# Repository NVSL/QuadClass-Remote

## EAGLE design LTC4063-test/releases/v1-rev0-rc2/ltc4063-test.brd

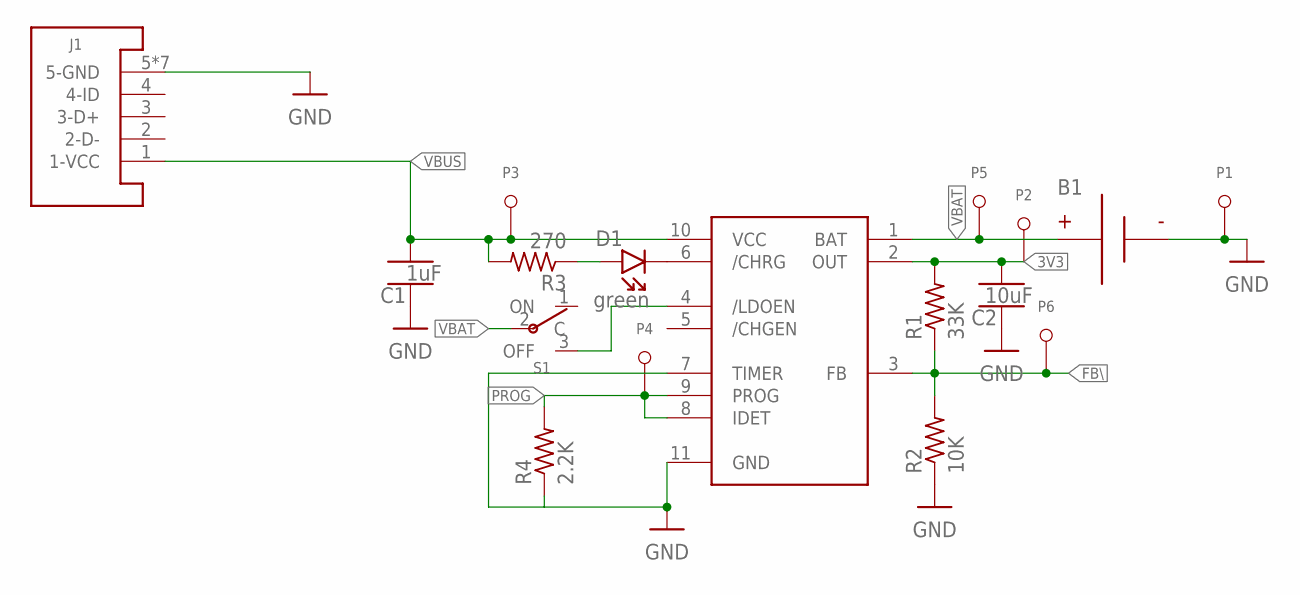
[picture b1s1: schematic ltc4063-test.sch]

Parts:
B1: BATTERY-SPRING-SMD; WIRE-TERMINAL-1X2-2.5MM-SMD-AVX-009276002021106
C1: 1uF; CAPC2012X140_HS
C2: 10uF; CAPC2012X140_HS
D1: green; LEDSC125X200X120-2_HS
J1: USB-MICROA-AMPHENOL-10118192-0001LF; USB-MICROA-10118192-0001LF
P1, P2, P3, P4, P5, P6: TEST-POINT; TEST-POINT-KEYSTONE-5000
R1: 33K; RESC2012X60_HS
R2: 10K; RESC2012X60_HS
R3: 270; RESC2012X60_HS
R4: 2.2K; RESC2012X60_HS
S1: POWER-SWITCH-MFS201N-9-Z-SMD-VERTICAL; JS102011JCQN
U1: LIPO-VREG-LTC4063; SON50P300X300X80-11T165X238

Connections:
3V3: C2.2, P2.T, R1.2, U1.2 (OUT)
FB\: P6.T, R1.1, R2.2, U1.3 (FB)
GND: B1.2A (N), B1.2B (N), C1.1, C2.1, J1.5 (5-GND), J1.6 (5-GND), J1.7 (5-GND), J1.8 (5-GND), J1.9 (5-GND), J1.10 (5-GND), J1.11 (5-GND), P1.T, R2.1, R4.1, U1.7 (TIMER), U1.11 (GND)
unnamed: S1.3 (OFF), U1.4 (/LDOEN)
unnamed: D1.C, U1.6 (/CHRG)
unnamed: D1.A, R3.1
PROG: P4.T, R4.2, U1.8 (IDET), U1.9 (PROG)
VBAT: B1.1A, B1.1B, P5.T, S1.2 (C), U1.1 (BAT)
VBUS: C1.2, J1.1 (1-VCC), P3.T, R3.2, U1.10 (VCC)

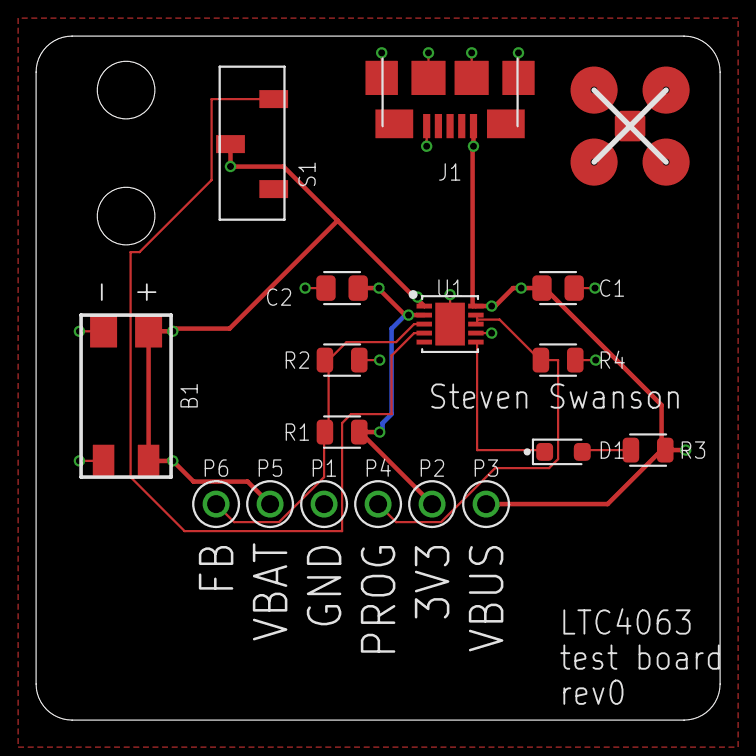
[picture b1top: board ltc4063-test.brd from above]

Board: 2 copper layers, 38.0 x 38.0 mm, 18 parts (0 on the bottom side), 9 nets.

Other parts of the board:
U$1: QUADCLASS_LOGO_SMALL

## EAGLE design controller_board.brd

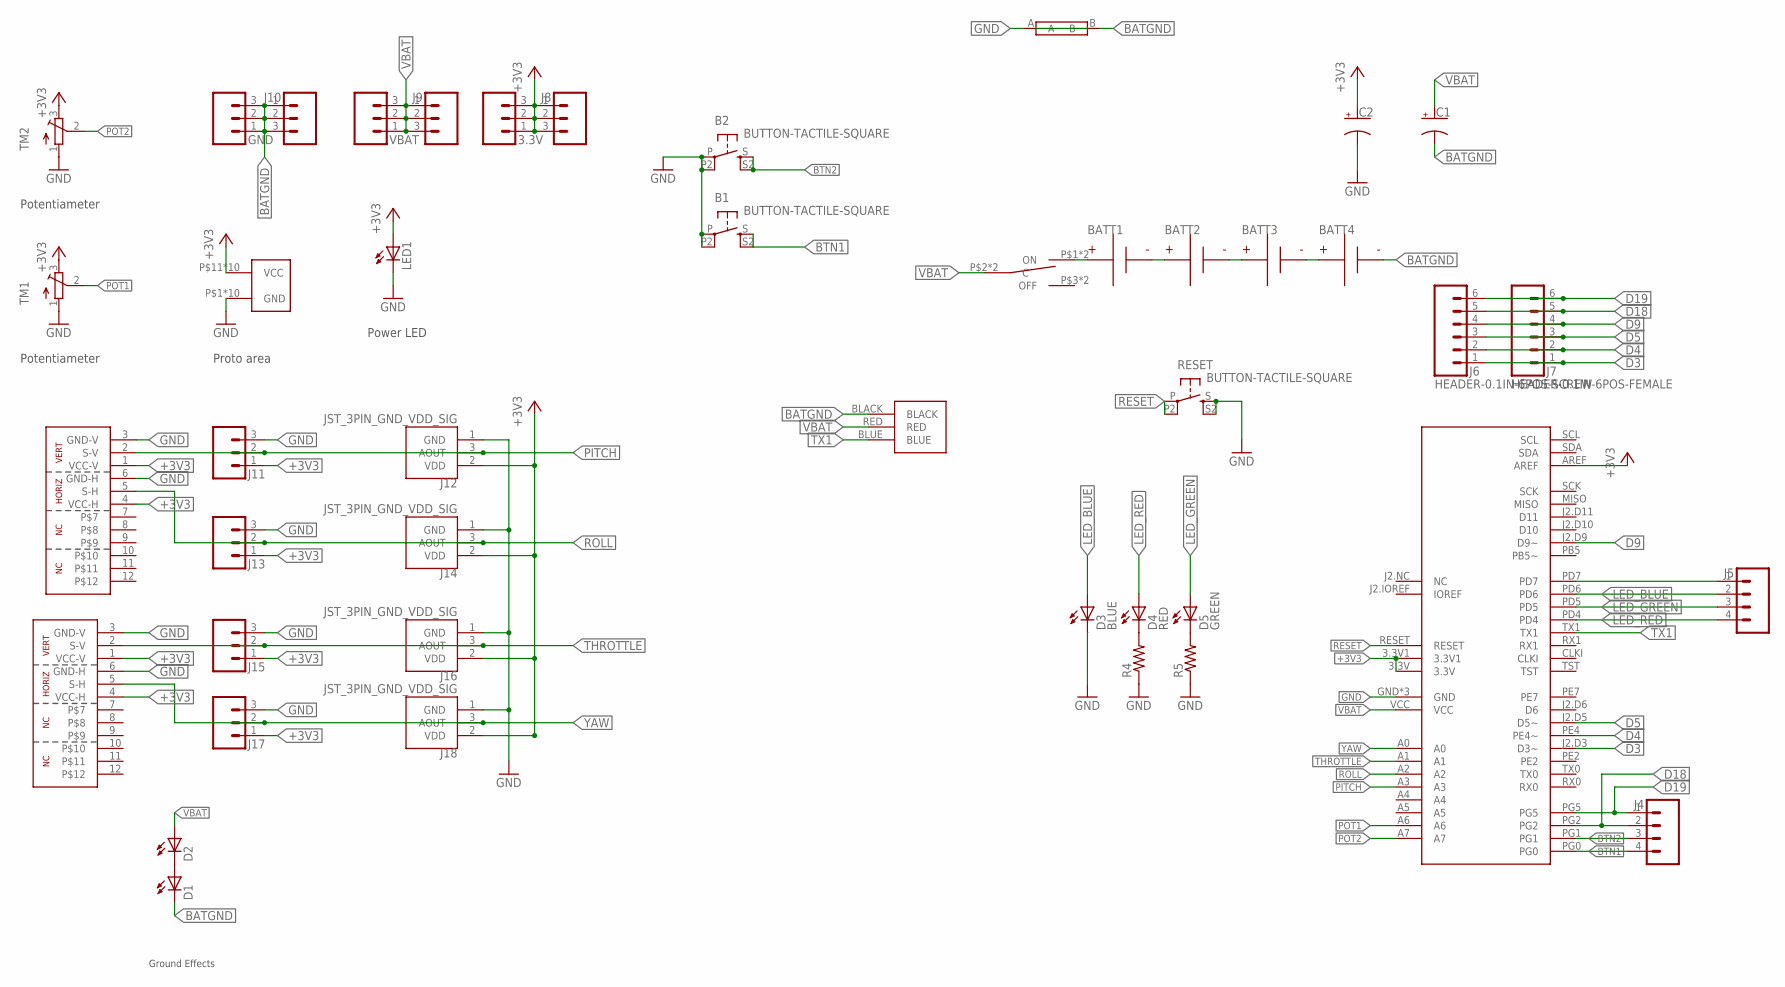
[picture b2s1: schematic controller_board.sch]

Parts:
3.3V: HEADER-0.1IN-3POS-SCREW; SCREW-TERMINAL-1X3-2.54MM
B1, B2: BUTTON-TACTILE-SQUARE; BUTTON-TACTILE-SQUARE-ADAFRUIT1010
BATT1, BATT2, BATT3, BATT4: BATTERY-AA-CLIP; BATTERY-AA-BK-92
C1: RESOLVED-CAPACITOR-POL_TH-RADIAL_ALUMINUM_18MM; CAPPRD750W80D1800H2200P
C2: RESOLVED-CAPACITOR-POL_TH-RADIAL_ALUMINUM_6.3MM; CAPPRD250W80D630H1220P
D1, D2: LED3MM
D3: BLUE; LED3MM
D4: RED; LED3MM
D5: GREEN; LED3MM
F1: SHORT
GND: HEADER-0.1IN-3POS-SCREW; SCREW-TERMINAL-1X3-2.54MM
J1, J2: FRSKY-GIMBAL; JST-13-PTH
J3: WIRE-HARNESS-SPARKFUN-9915
J4, J5: HEADER-0.1IN-4POS-FEMALE; HDRV4W63P254_4X1_1016X254H838_HS
J6: HEADER-0.1IN-6POS-SCREW; SCREW-TERMINAL-1X6-2.54MM
J7: HEADER-0.1IN-6POS-FEMALE; HDRV6W63P254_6X1_1524X254H838_HS
J8, J9, J10: HEADER-0.1IN-3POS-FEMALE; HDRV3W63P254_3X1_762X254H838_HS
J11, J13, J15, J17: HEADER-0.1IN-3POS-SCREW; SCREW-TERMINAL-1X3-2.54MM
J12, J14, J16, J18: JST_3PIN_GND_VDD_SIG; JST-3-PTH-REVERSE
LED1: LED-5MM-RED; LED5MM
R4, R5: RESOLVED-RESISTOR_TH-1/6W-CARBON; RESAD770W45L370D210_HS
RESET: BUTTON-TACTILE-SQUARE; BUTTON-TACTILE-SQUARE-ADAFRUIT1010
S1: POWER-SWITCH-MFS201N-9-Z
TM1, TM2: TRIMPOT3386; TRIM-3386
U$3: PROTO-AREA-10X10
U$4: ATMEGA128RFA1-BOB; ATMEGA128RFA1
VBAT: HEADER-0.1IN-3POS-SCREW; SCREW-TERMINAL-1X3-2.54MM

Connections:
+3V3: 3.3V.1, 3.3V.2, 3.3V.3, C2.1 (+), J1.1 (VCC-V), J1.4 (VCC-H), J2.1 (VCC-V), J2.4 (VCC-H), J8.1, J8.2, J8.3, J11.1, J12.2 (VDD), J13.1, J14.2 (VDD), J15.1, J16.2 (VDD), J17.1, J18.2 (VDD), LED1.A, TM1.3 (E), TM2.3 (E), U$3.P$11 (VCC), U$3.P$12 (VCC), U$3.P$13 (VCC), U$3.P$14 (VCC), U$3.P$15 (VCC), U$3.P$16 (VCC), U$3.P$17 (VCC), U$3.P$18 (VCC), U$3.P$19 (VCC), U$3.P$20 (VCC), U$4.3.3V, U$4.3.3V1, U$4.AREF
BATGND: BATT4.N1 (N), BATT4.N2 (N), C1.2 (-), D1.K (C), F1.B, GND.1, GND.2, GND.3, J3.BLACK, J10.1, J10.2, J10.3
BTN1: B1.S, B1.S2 (S1), J4.4, U$4.PG0
BTN2: B2.S, B2.S2 (S1), J4.3, U$4.PG1
D3: J6.1, J7.1, U$4.J2.D3 (D3~)
D4: J6.2, J7.2, U$4.PE4 (PE4~)
D5: J6.3, J7.3, U$4.J2.D5 (D5~)
D9: J6.4, J7.4, U$4.J2.D9 (D9~)
D18: J4.2, J6.5, J7.5, U$4.PG2
D19: J4.1, J6.6, J7.6, U$4.PG5
GND: B1.P, B1.P2 (P1), B2.P, B2.P2 (P1), C2.2 (-), D3.K (C), F1.A, J1.3 (GND-V), J1.6 (GND-H), J2.3 (GND-V), J2.6 (GND-H), J11.3, J12.1 (GND), J13.3, J14.1 (GND), J15.3, J16.1 (GND), J17.3, J18.1 (GND), LED1.K (C), R4.1, R5.1, RESET.S, RESET.S2 (S1), TM1.1 (A), TM2.1 (A), U$3.P$1 (GND), U$3.P$2 (GND), U$3.P$3 (GND), U$3.P$4 (GND), U$3.P$5 (GND), U$3.P$6 (GND), U$3.P$7 (GND), U$3.P$8 (GND), U$3.P$9 (GND), U$3.P$10 (GND), U$4.GND, U$4.GND1 (GND), U$4.GND2 (GND)
LED_BLUE: D3.A, J5.2, U$4.PD6
LED_GREEN: D5.A, J5.3, U$4.PD5
LED_RED: D4.A, J5.4, U$4.PD4
unnamed: BATT1.N1 (N), BATT1.N2 (N), BATT2.P1, BATT2.P2
unnamed: BATT2.N1 (N), BATT2.N2 (N), BATT3.P1, BATT3.P2
unnamed: BATT3.N1 (N), BATT3.N2 (N), BATT4.P1, BATT4.P2
unnamed: D4.K (C), R4.2
unnamed: BATT1.P1, BATT1.P2, S1.P$1 (ON), S1.P$4 (ON)
unnamed: D5.K (C), R5.2
unnamed: J5.1, U$4.PD7
unnamed: D1.A, D2.K (C)
PITCH: J1.2 (S-V), J11.2, J12.3 (AOUT), U$4.A3
POT1: TM1.2 (S), U$4.A6
POT2: TM2.2 (S), U$4.A7
RESET: RESET.P, RESET.P2 (P1), U$4.RESET
ROLL: J1.5 (S-H), J13.2, J14.3 (AOUT), U$4.A2
THROTTLE: J2.2 (S-V), J15.2, J16.3 (AOUT), U$4.A1
TX1: J3.BLUE, U$4.TX1
VBAT: C1.1 (+), D2.A, J3.RED, J9.1, J9.2, J9.3, S1.P$2 (C), S1.P$5 (C), U$4.VCC, VBAT.1, VBAT.2, VBAT.3
YAW: J2.5 (S-H), J17.2, J18.3 (AOUT), U$4.A0

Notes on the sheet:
Potentiameter
Proto area
Power LED
Ground Effects

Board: 2 copper layers, 48 parts (10 on the bottom side), 31 nets, no tracks yet.

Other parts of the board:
LCD: SPARKFUN_LCD_33
OUTLINE: CONTROLLER_OUTLINE
U$1: CSE_LOGO_30X20MM
U$2: UCSD_LOGO_COMBINED_26X20MM

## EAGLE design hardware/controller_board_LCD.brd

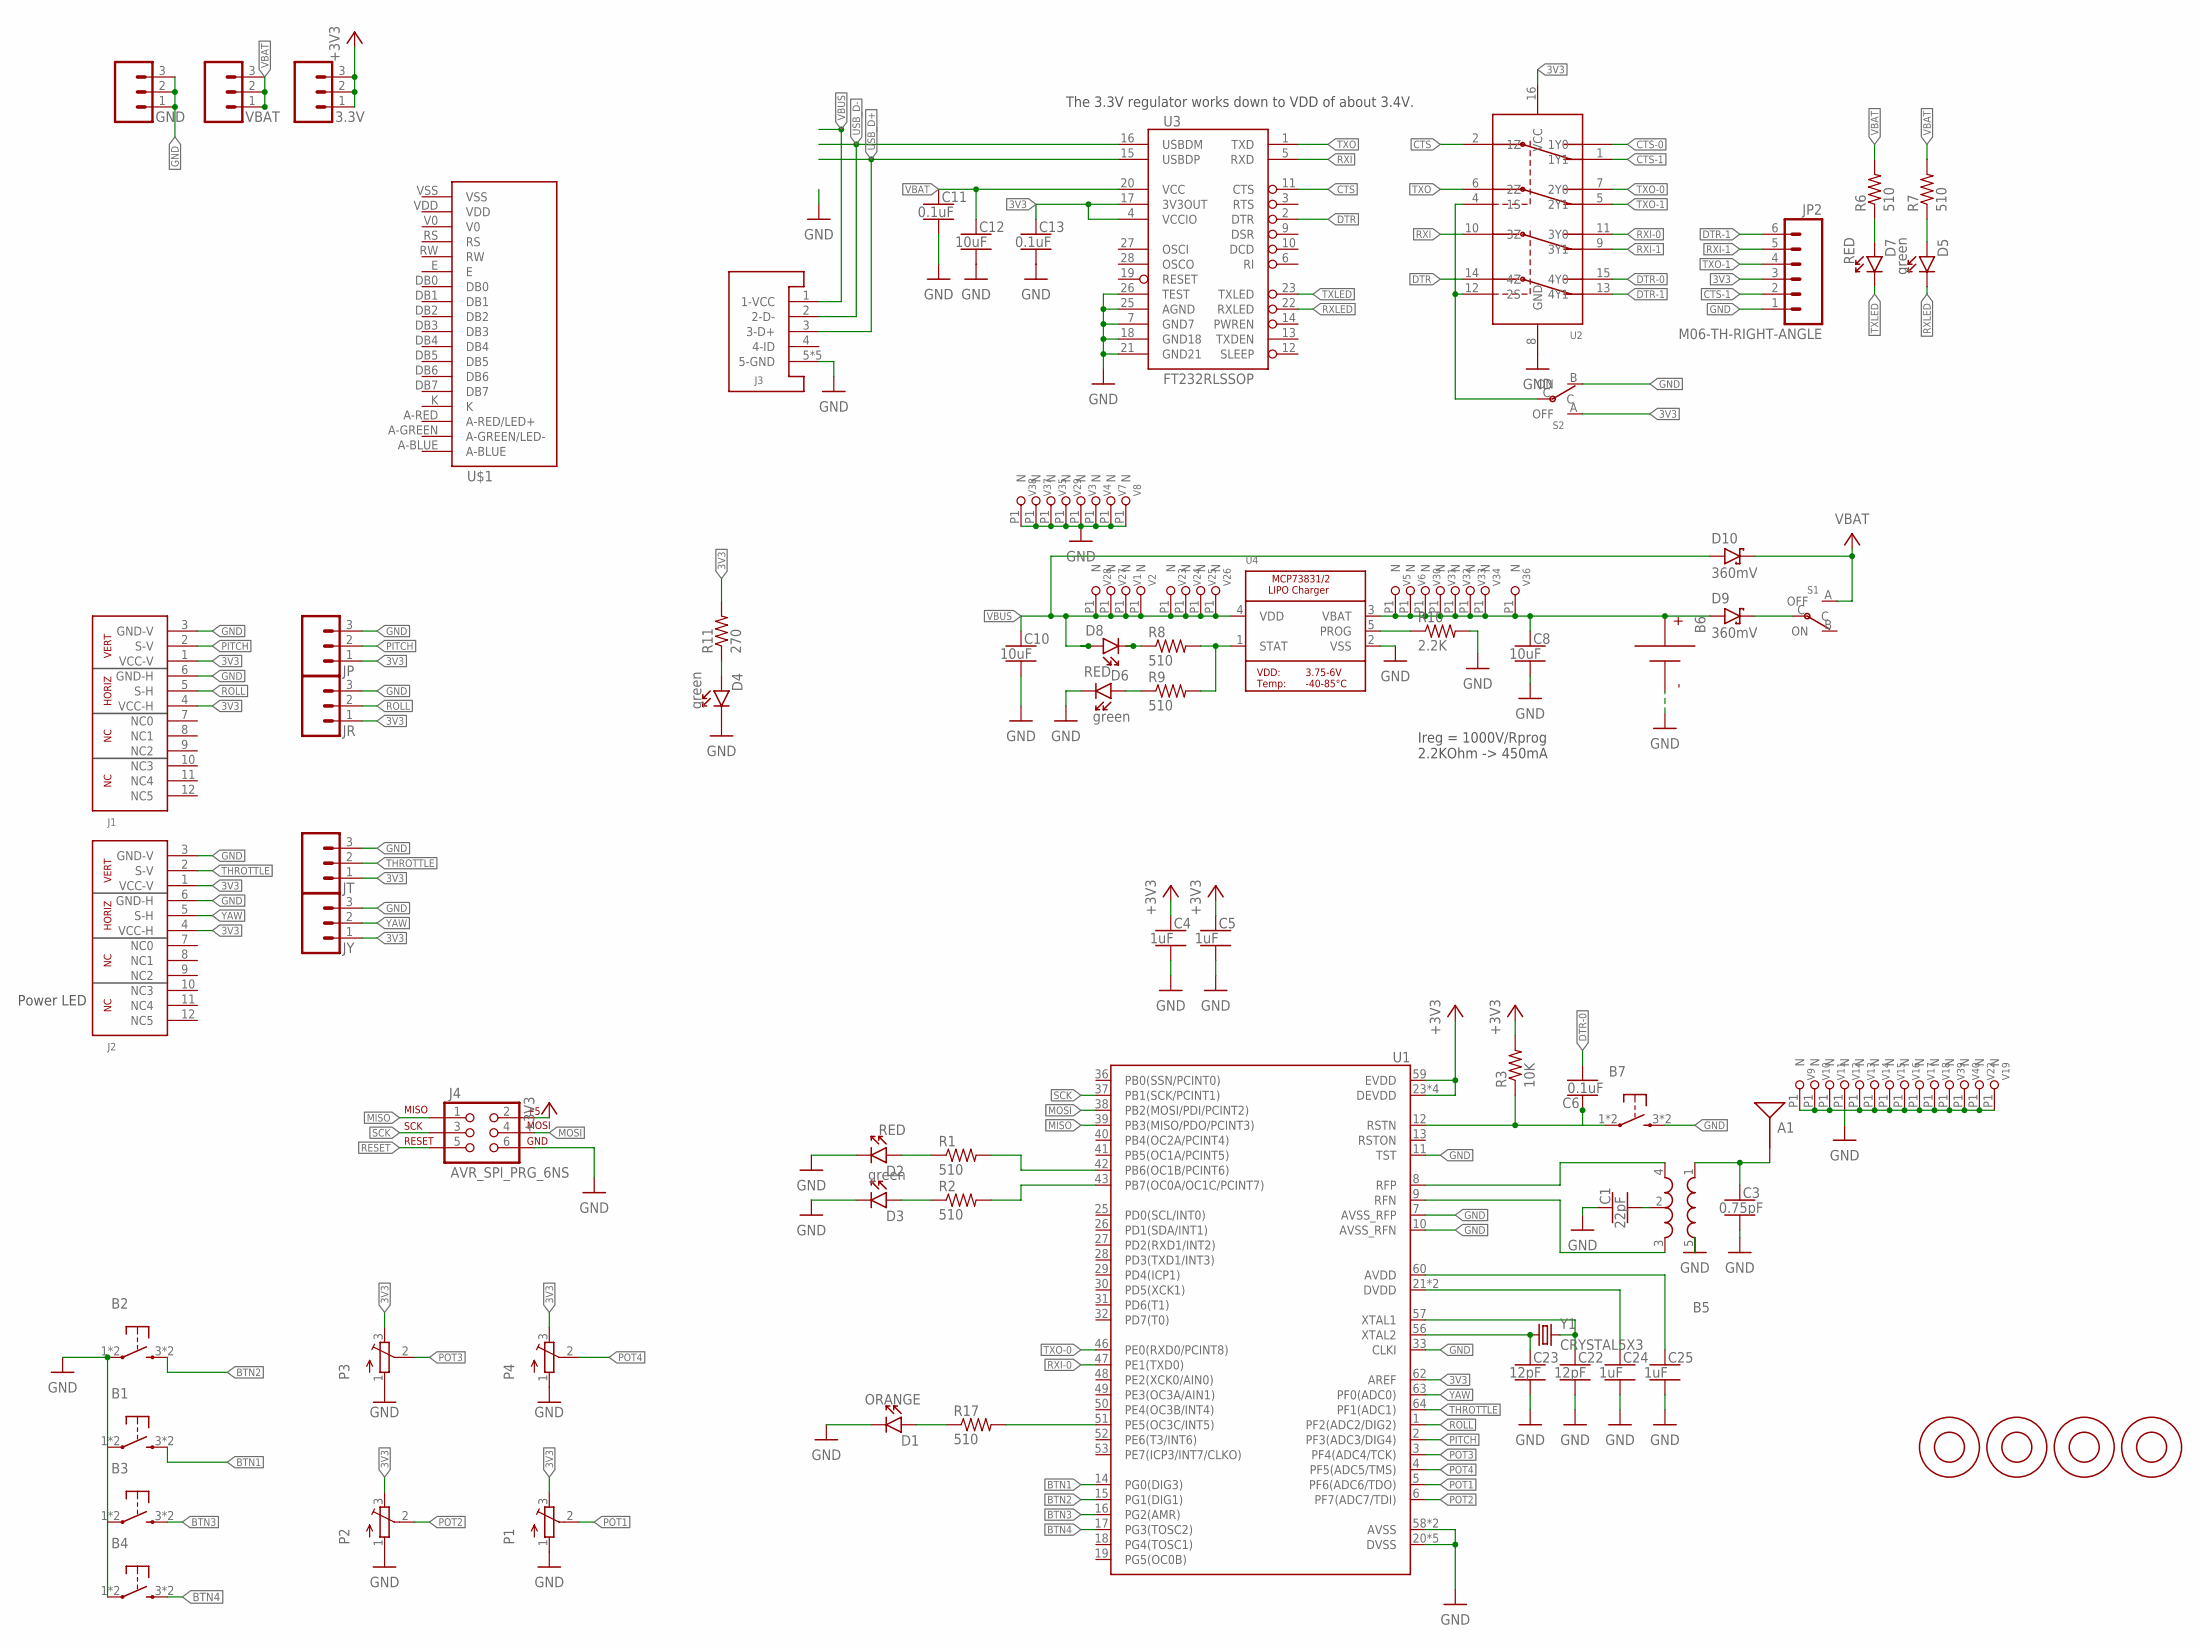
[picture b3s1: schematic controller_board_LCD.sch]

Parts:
3.3V: HEADER-0.1IN-3POS-SCREW; SCREW-TERMINAL-1X3-2.54MM
A1: ANTENNA2SMD5; ANTENNA-CHIP5
B1, B2, B3, B4, B7: PUSHBUTTON_SMD-VERTICAL-1; TE_FSM8JSMA_HS
B5: BALUN0805; BALUN
B6: BATTERY; BATTERY-TERMINALS
C1: 22pF; CAPC2012X140_HS
C3: 0.75pF; CAPC2012X140_HS
C4, C5, C24, C25: 1uF; CAPC2012X140_HS
C6, C11, C13: 0.1uF; CAPC2012X140_HS
C8, C10, C12: 10uF; CAPC2012X140_HS
C22, C23: 12pF; CAPC2012X140_HS
D1: ORANGE; LEDSC125X200X120-2_HS
D2, D7, D8: RED; LEDSC125X200X120-2_HS
D3, D4, D5, D6: green; LEDSC125X200X120-2_HS
D9, D10: 360mV; SOD3716X135_HS
F1, F2, F3, F4: 1mm; FIDUCIAL_STENCIL
GND: HEADER-0.1IN-3POS-SCREW; SCREW-TERMINAL-1X3-2.54MM
J1, J2: FRSKY-GIMBAL; JST-13-PTH
J3: USB-MICROB-EDAC-690-005-299-043; USB-MINIB-EDAC-690-005-299-043
J4: AVR_SPI_PRG_6NS; 2X3-NS
JP: HEADER-0.1IN-3POS-SCREW; SCREW-TERMINAL-1X3-2.54MM
JP2: M06-TH-RIGHT-ANGLE; 1X06-SIP-RIGHT-ANGLE
JR: HEADER-0.1IN-3POS-SCREW; SCREW-TERMINAL-1X3-2.54MM
JT: HEADER-0.1IN-3POS-SCREW; SCREW-TERMINAL-1X3-2.54MM
JY: HEADER-0.1IN-3POS-SCREW; SCREW-TERMINAL-1X3-2.54MM
P1, P2, P3, P4: TRIMPOT3386; TRIM-3386
R1, R2, R6, R7, R8, R9, R17: 510; RESC2012X60_HS
R3: 10K; RESC2012X60_HS
R10: 2.2K; RESC2012X60_HS
R11: 270; RESC2012X60_HS
S1, S2: POWER-SWITCH-MFS201N-9-ZJS102011SAQN; JS102011SAQN
U1: ATMEGA128RFA1; QFN-64
U2: DPDT-X2; SOP65P640X110-16
U3: FT232RLSSOP; SSOP28DB
U4: MCP73831T-2ACI/OT; SOT23-5
U$1: SPARKFUN_LCD_33_SERIAL-RGB; SPARKFUN_LCD_33_PARALLEL
V1, V2, V3, V4, V5, V6, V7, V8, V9, V10, V11, V12, V13, V14, V15, V16, V17, V18, V19, V22, V23, V24, V25, V26, V27, V28, V29, V30, V31, V32, V33, V34, V35, V36, V37, V38, V39, V40: LOCKED-VIA-0.2; VIA-0.2MM
VBAT: HEADER-0.1IN-3POS-SCREW; SCREW-TERMINAL-1X3-2.54MM
Y1: CRYSTAL5X3; CRYSTAL-SMD-5X3

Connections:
3V3: 3.3V.1, 3.3V.2, 3.3V.3, C4.1, C5.1, C13.1, J1.1 (VCC-V), J1.4 (VCC-H), J2.1 (VCC-V), J2.4 (VCC-H), J4.2, JP.1, JP2.3, JR.1, JT.1, JY.1, P1.3 (E), P2.3 (E), P3.3 (E), P4.3 (E), R3.2, R11.2, S2.A (OFF), U1.23 (DEVDD), U1.34 (DEVDD), U1.44 (DEVDD), U1.54 (DEVDD), U1.59 (EVDD), U1.62 (AREF), U2.16 (VCC), U3.4 (VCCIO), U3.17 (3V3OUT)
ANTENNA: A1.FEED, B5.1 (IN), C3.1
BPOS: B6.+, C8.1, D9.A, U4.3 (VBAT), V5.P1, V6.P1, V30.P1, V31.P1, V32.P1, V33.P1, V34.P1, V36.P1
BTN1: B1.3 (2), B1.4 (2), U1.14 (PG0(DIG3))
BTN2: B2.3 (2), B2.4 (2), U1.15 (PG1(DIG1))
BTN3: B3.3 (2), B3.4 (2), U1.16 (PG2(AMR))
BTN4: B4.3 (2), B4.4 (2), U1.17 (PG3(TOSC2))
CTS: U2.2 (1Z), U3.11 (CTS)
CTS-0: U2.3 (1Y0)
CTS-1: JP2.2, U2.1 (1Y1)
DTR: U2.14 (4Z), U3.2 (DTR)
DTR-0: C6.2, U2.15 (4Y0)
DTR-1: JP2.6, U2.13 (4Y1)
GND: B1.1, B1.2 (1), B2.1, B2.2 (1), B3.1, B3.2 (1), B4.1, B4.2 (1), B5.5 (GND), B6.- (N), B7.3 (2), B7.4 (2), C1.1, C3.2, C4.2, C5.2, C8.2, C10.2, C11.2, C12.2, C13.2, C22.2, C23.2, C24.2, C25.2, D1.1 (C), D2.2 (C), D3.1 (C), D4.1 (C), D6.1 (C), GND.1, GND.2, GND.3, J1.3 (GND-V), J1.6 (GND-H), J2.3 (GND-V), J2.6 (GND-H), J3.5 (5-GND), J3.P6 (5-GND), J3.P7 (5-GND), J3.P8 (5-GND), J3.P9 (5-GND), J4.6, JP.3, JP2.1, JR.3, JT.3, JY.3, P1.1 (A), P2.1 (A), P3.1 (A), P4.1 (A), R10.2, S2.B (ON), U1.7 (AVSS_RFP), U1.10 (AVSS_RFN), U1.11 (TST), U1.20 (DVSS), U1.24 (DVSS), U1.33 (CLKI), U1.35 (DVSS), U1.45 (DVSS), U1.55 (DVSS), U1.58 (AVSS), U1.61 (AVSS), U2.8 (GND), U3.7 (GND7), U3.18 (GND18), U3.21 (GND21), U3.25 (AGND), U3.26 (TEST), U4.2 (VSS), V3.P1, V4.P1, V7.P1, V8.P1, V9.P1, V10.P1, V11.P1, V12.P1, V13.P1, V14.P1, V15.P1, V16.P1, V17.P1, V18.P1, V19.P1, V22.P1, V29.P1, V35.P1, V37.P1, V38.P1, V39.P1, V40.P1
MISO: J4.1, U1.39 (PB3(MISO/PDO/PCINT3))
MOSI: J4.4, U1.38 (PB2(MOSI/PDI/PCINT2))
unnamed: D9.C, S1.C
unnamed: D7.1 (A), R6.1
unnamed: D5.2 (A), R7.1
unnamed: R2.2, U1.43 (PB7(OC0A/OC1C/PCINT7))
unnamed: D8.2 (C), R8.1
unnamed: B5.2 (GND), C1.2
unnamed: R1.2, U1.42 (PB6(OC1B/PCINT6))
unnamed: D2.1 (A), R1.1
unnamed: D3.2 (A), R2.1
unnamed: R8.2, R9.2, U4.1 (STAT)
unnamed: R10.1, U4.5 (PROG)
unnamed: D6.2 (A), R9.1
unnamed: D4.2 (A), R11.1
unnamed: C22.1, U1.57 (XTAL1), Y1.3 (2)
unnamed: R17.2, U1.51 (PE5(OC3C/INT5))
unnamed: D1.2 (A), R17.1
unnamed: C23.1, U1.56 (XTAL2), Y1.1
unnamed: C24.1, U1.21 (DVDD), U1.22 (DVDD)
unnamed: C25.1, U1.60 (AVDD)
PITCH: J1.2 (S-V), JP.2, U1.2 (PF3(ADC3/DIG4))
POT1: P1.2 (S), U1.5 (PF6(ADC6/TDO))
POT2: P2.2 (S), U1.6 (PF7(ADC7/TDI))
POT3: P3.2 (S), U1.3 (PF4(ADC4/TCK))
POT4: P4.2 (S), U1.4 (PF5(ADC5/TMS))
PROG_SEL: S2.C, U2.4 (1S), U2.12 (2S)
RESET: B7.1, B7.2 (1), C6.1, J4.5, R3.1, U1.12 (RSTN)
RFN: B5.3 (OUT2), U1.9 (RFN)
RFP: B5.4 (OUT1), U1.8 (RFP)
ROLL: J1.5 (S-H), JR.2, U1.1 (PF2(ADC2/DIG2))
RXI: U2.10 (3Z), U3.5 (RXD)
RXI-0: U1.47 (PE1(TXD0)), U2.11 (3Y0)
RXI-1: JP2.5, U2.9 (3Y1)
RXLED: D5.1 (C), U3.22 (RXLED)
SCK: J4.3, U1.37 (PB1(SCK/PCINT1))
THROTTLE: J2.2 (S-V), JT.2, U1.64 (PF1(ADC1))
TXLED: D7.2 (C), U3.23 (TXLED)
TXO: U2.6 (2Z), U3.1 (TXD)
TXO-0: U1.46 (PE0(RXD0/PCINT8)), U2.7 (2Y0)
TXO-1: JP2.4, U2.5 (2Y1)
USB_D+: J3.3 (3-D+), U3.15 (USBDP)
USB_D-: J3.2 (2-D-), U3.16 (USBDM)
VBAT: C11.1, C12.1, D10.C, R6.2, R7.2, S1.A (OFF), U3.20 (VCC), VBAT.1, VBAT.2, VBAT.3
VBUS: C10.1, D8.1 (A), D10.A, J3.1 (1-VCC), U4.4 (VDD), V1.P1, V2.P1, V23.P1, V24.P1, V25.P1, V26.P1, V27.P1, V28.P1
YAW: J2.5 (S-H), JY.2, U1.63 (PF0(ADC0))

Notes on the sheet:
Power LED
Ireg = 1000V/Rprog 2.2KOhm -> 450mA
The 3.3V regulator works down to VDD of about 3.4V.

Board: 4 copper layers, 110 parts (6 on the bottom side), 59 nets, no tracks yet.

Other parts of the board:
E$1, E$2: FRSKY-TARANIS-GIMBAL

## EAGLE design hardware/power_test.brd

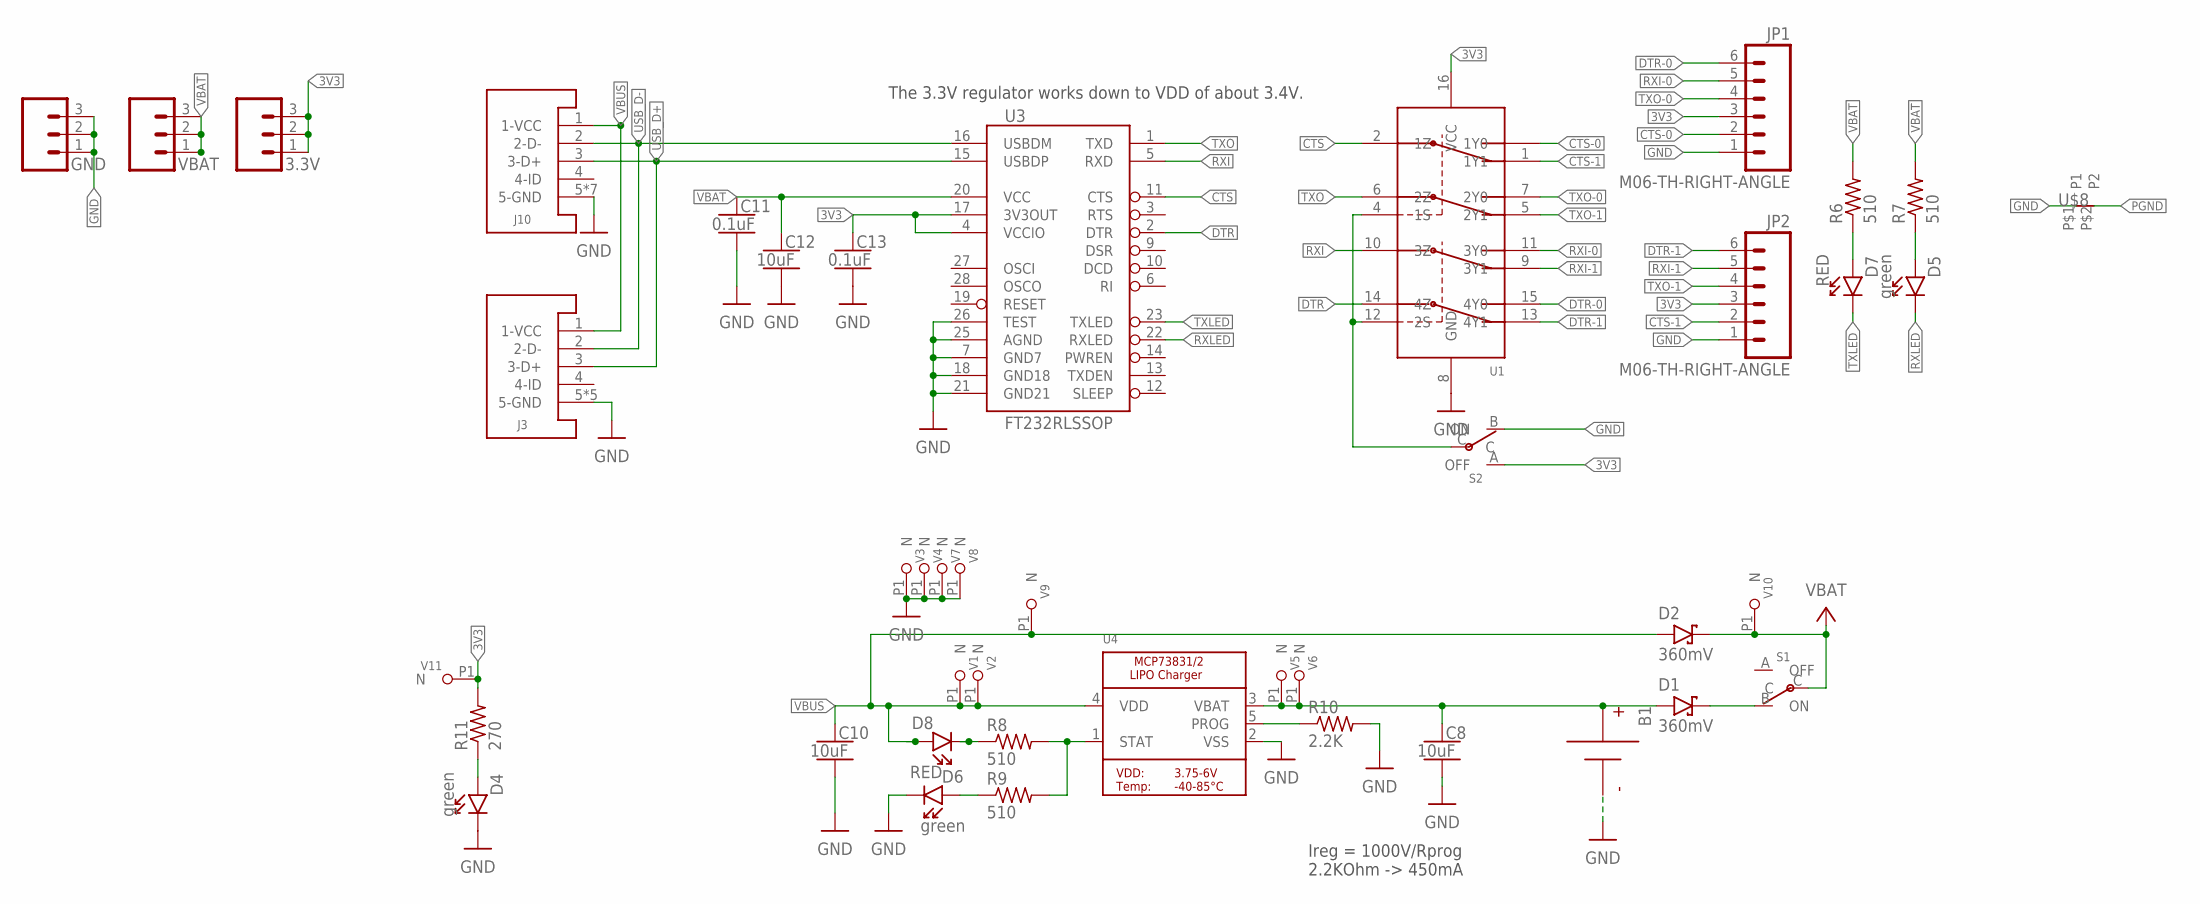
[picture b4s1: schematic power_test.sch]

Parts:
3.3V: HEADER-0.1IN-3POS-MALE; HDRV3W63P254_3X1_762X254H838_HS
B1: BATTERY; BATTERY-TERMINALS
C8, C10, C12: 10uF; CAPC2012X140_HS
C11, C13: 0.1uF; CAPC2012X140_HS
D1, D2: 360mV; SOD3716X135_HS
D4, D5, D6: green; LEDSC125X200X120-2_HS
D7, D8: RED; LEDSC125X200X120-2_HS
GND: HEADER-0.1IN-3POS-MALE; HDRV3W63P254_3X1_762X254H838_HS
J3: USB-MICROB-EDAC-690-005-299-043; USB-MINIB-EDAC-690-005-299-043
J10: USB-MICROA-AMPHENOL-10118192-0001LF; USB-MICROA-10118192-0001LF
JP1, JP2: M06-TH-RIGHT-ANGLE; 1X06-SIP-RIGHT-ANGLE
R6, R7, R8, R9: 510; RESC2012X60_HS
R10: 2.2K; RESC2012X60_HS
R11: 270; RESC2012X60_HS
S1, S2: POWER-SWITCH-MFS201N-9-ZJS102011SAQN; JS102011SAQN
U1: DPDT-X2; SOP65P640X110-16
U3: FT232RLSSOP; SSOP28DB
U4: MCP73831T-2ACI/OT; SOT23-5
U$8: NET_BRIDGE
V1, V2, V3, V4, V5, V6, V7, V8, V9, V10, V11: LOCKED-VIA-0.2; VIA-0.2MM
VBAT: HEADER-0.1IN-3POS-MALE; HDRV3W63P254_3X1_762X254H838_HS

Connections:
3V3: 3.3V.1, 3.3V.2, 3.3V.3, C13.1, JP1.3, JP2.3, R11.2, S2.A (OFF), U1.16 (VCC), U3.4 (VCCIO), U3.17 (3V3OUT), V11.P1
BPOS: B1.+, C8.1, D1.A, U4.3 (VBAT), V5.P1, V6.P1
CTS: U1.2 (1Z), U3.11 (CTS)
CTS-0: JP1.2, U1.3 (1Y0)
CTS-1: JP2.2, U1.1 (1Y1)
DTR: U1.14 (4Z), U3.2 (DTR)
DTR-0: JP1.6, U1.15 (4Y0)
DTR-1: JP2.6, U1.13 (4Y1)
GND: B1.- (N), C8.2, C10.2, C11.2, C12.2, C13.2, D4.C, D6.C, GND.1, GND.2, GND.3, J3.5 (5-GND), J3.P6 (5-GND), J3.P7 (5-GND), J3.P8 (5-GND), J3.P9 (5-GND), J10.5 (5-GND), J10.6 (5-GND), J10.7 (5-GND), J10.8 (5-GND), J10.9 (5-GND), J10.10 (5-GND), J10.11 (5-GND), JP1.1, JP2.1, R10.2, S2.B (ON), U1.8 (GND), U3.7 (GND7), U3.18 (GND18), U3.21 (GND21), U3.25 (AGND), U3.26 (TEST), U4.2 (VSS), U$8.P$1 (P1), V3.P1, V4.P1, V7.P1, V8.P1
unnamed: D7.A, R6.1
unnamed: D5.A, R7.1
unnamed: D8.C, R8.1
unnamed: R8.2, R9.2, U4.1 (STAT)
unnamed: R10.1, U4.5 (PROG)
unnamed: D6.A, R9.1
unnamed: D4.A, R11.1
unnamed: D1.C, S1.B (ON)
PGND: U$8.P$2 (P2)
PROG_SEL: S2.C, U1.4 (1S), U1.12 (2S)
RXI: U1.10 (3Z), U3.5 (RXD)
RXI-0: JP1.5, U1.11 (3Y0)
RXI-1: JP2.5, U1.9 (3Y1)
RXLED: D5.C, U3.22 (RXLED)
TXLED: D7.C, U3.23 (TXLED)
TXO: U1.6 (2Z), U3.1 (TXD)
TXO-0: JP1.4, U1.7 (2Y0)
TXO-1: JP2.4, U1.5 (2Y1)
USB_D+: J3.3 (3-D+), J10.3 (3-D+), U3.15 (USBDP)
USB_D-: J3.2 (2-D-), J10.2 (2-D-), U3.16 (USBDM)
VBAT: C11.1, C12.1, D2.C, R6.2, R7.2, S1.C, U3.20 (VCC), V10.P1, VBAT.1, VBAT.2, VBAT.3
VBUS: C10.1, D2.A, D8.A, J3.1 (1-VCC), J10.1 (1-VCC), U4.4 (VDD), V1.P1, V2.P1, V9.P1

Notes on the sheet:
Ireg = 1000V/Rprog 2.2KOhm -> 450mA
The 3.3V regulator works down to VDD of about 3.4V.

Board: 4 copper layers, 43 parts (1 on the bottom side), 30 nets, no tracks yet.

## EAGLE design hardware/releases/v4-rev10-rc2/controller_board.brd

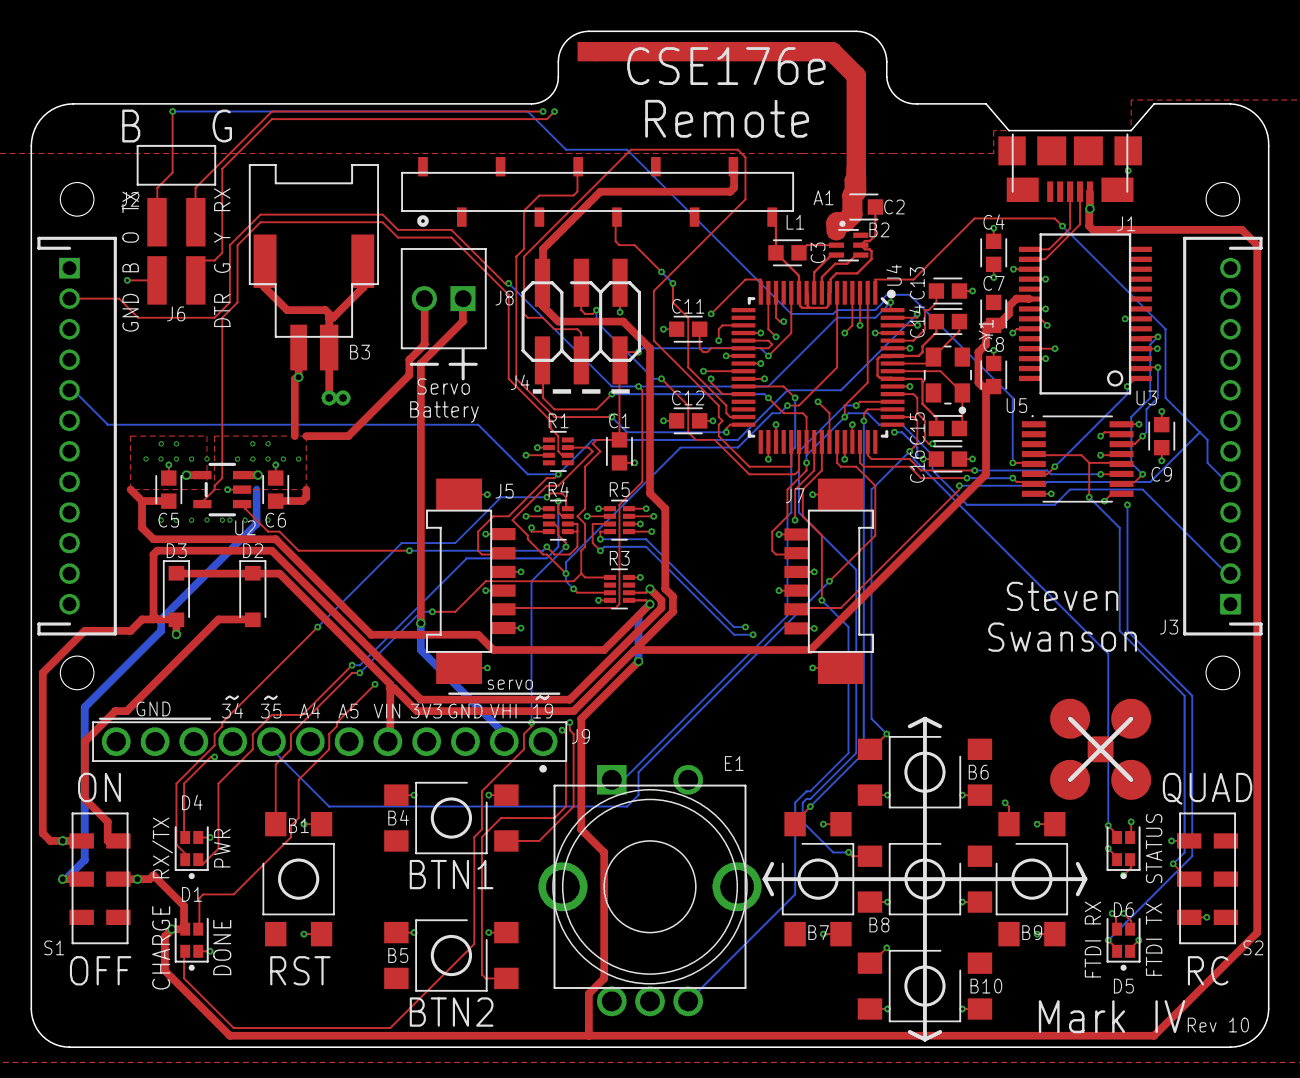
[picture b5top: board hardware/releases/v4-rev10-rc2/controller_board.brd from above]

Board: 4 copper layers, 81.0 x 66.5 mm, 84 parts (0 on the bottom side), 70 nets.

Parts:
A1: ANTENNA-BOARD-REV; ANT_PCB_2.4GHZ_NRF8001_1.6MM_1OZ_REV
B1, B4, B5, B6, B7, B8, B9, B10: PUSHBUTTON_-4.5X4.5; 4.5MM_TACTILE_SWITCH_TL3305AF160QG
B2: BALUN0805; BALUN
B3: BATTERY-SMD; MOLEX-BATTERY-CONNECTOR-SMD-51005-2P
C1, C8, C9: 0.1uF; CAPC1608X100
C2: 0.75pF; CAPC1608X100
C3: 22pF; CAPC1608X100
C4, C11, C12, C13, C16: 1uF; CAPC1608X100
C5, C6, C7: 10uF; CAPC1608X100
C14, C15: 12pF; CAPC1608X100
D1, D4, D5, D6: LED-2X-GREEN/RED-1.6X1.5MM; LED-2X-LITE-ON-1.6MMX1.5MM
D2, D3: 360mV; SODFL3516X96
E1: ROTARY-ENCODER-W/BUTTON-BOURNS-PEC12R-4217F; BOURNS-PEC12R
E$1, E$2: FRSKY-TARANIS-GIMBAL
F1: SHORT
J1: USB-MICROA-AMPHENOL-10118192-0001LF; USB-MICROA-10118192-0001LF
J2, J3: 2.4K; JST-13-PTH
J4: AVR_SPI_PRG_6-SMD; 2X3-SMD
J5, J7: FRSKY-GIMBAL-FRYSKY-HALL-EFFECT; MOLEX-0532610671
J6: FTDI-4PIN-RIGHT-ANGLE-SMD; HEADER-2X2-0.1IN-MALE-RIGHT-ANGLE-SMD
J8: HEADER-0.1IN-2POS-SCREW; SCREW-TERMINAL-1X2-2.54MM
J9: HEADER-12POS-0.1IN-FEMALE-TH; HDRVR12W75P254_1X12_3098X254X850B
L1: SPARKFUN_SERLCD_SERIAL_REDUCED-SMD; SPARKFUN_SERLCD_16X2_REDUCED_SMD
R1: 2.2K; RESCAXS50P200X100X45-8
R3: 10K; RESCAXS50P200X100X45-8
R4, R5: 1.5K; RESCAXS50P200X100X45-8
S1, S2: SWITCH-DPDT-300MA-6V-SMD; JS202011JCQN
U2: MCP73831T-2ACI/OT; SOT23-5
U3: FT232RLSSOP; SSOP28DB
U4: ATMEGA128RFA1; QFN-64
U5: DPDT-X2; SOP65P640X110-16
U$1: 700MAH-BATTERY
U$2: QUADCLASS_LOGO_SMALL
U$3: LAYER_LABELS
U$4: 375MAH-BATTERY
U$5: 600MAH-BATTERY
V1, V2, V3, V4, V5, V6, V7, V8, V23, V24, V26, V27, V28, V30, V31, V32, V33, V34, V35, V36, V37, V38: LOCKED-VIA-0.2; VIA-0.2MM
Y1: CRYSTAL-SMD-3X2; OSCCC320X250X85

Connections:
3V3: C4.2, C9.1, C12.1, C16.1, D4.A1, J2.1, J2.4, J3.1, J3.4, J5.3, J5.6, J7.3, J7.6, J9.4, R3.8, R5.5, R5.6, S2.3, U3.4, U3.17, U4.23, U4.34, U4.44, U4.54, U4.59, U4.62, U5.16
19: J9.1, U4.19
34: J9.9, U4.42
35: J9.8, U4.43
A4: J9.7, U4.3
A5: J9.6, U4.4
ANTENNA: A1.FEED, B2.1, C2.1
BAT_SENSE: R1.7, R3.3, U4.6
BCAP: B2.2, C3.2
BPOS: B3.P, C6.1, J8.2, S1.2, U2.3, V6.P1, V30.P1, V31.P1, V32.P1, V33.P1, V34.P1, V36.P1
BTN1/SCL: B4.3, B4.4, U4.25
BTN2/SDA: B5.3, B5.4, U4.26
BTN_CENTER: B9.1, B9.2, U4.53
BTN_DOWN: B10.1, B10.2, U4.28
BTN_LEFT: B7.1, B7.2, U4.51
BTN_RIGHT: B8.1, B8.2, U4.52
BTN_UP: B6.1, B6.2, U4.50
CLK_NEG: C15.1, U4.56, Y1.1
CLK_POS: C14.1, U4.57, Y1.3
DTR: U3.2, U5.14
DTR-0: C1.2, U5.15
DTR-1: J6.DTR, U5.13
E1-A: E1.A, U4.40
E1-B: E1.B, U4.41
E1-BUT: E1.BUTA, U4.27
GND: B1.3, B1.4, B2.5, B4.1, B4.2, B5.1, B5.2, B6.3, B6.4, B7.3, B7.4, B8.3, B8.4, B9.3, B9.4, B10.3, B10.4, C2.2, C3.1, C4.1, C5.2, C6.2, C7.2, C8.2, C9.2, C11.2, C12.2, C13.2, C14.2, C15.2, C16.2, D1.C1, E1.BUTB, E1.C, F1.2, J1.5, J1.6, J1.7, J1.8, J1.9, J1.10, J1.11, J2.3, J2.6, J3.3, J3.6, J4.6, J5.1, J5.4, J5.G1, J5.G2, J6.GND, J7.1, J7.4, J7.G1, J7.G2, J9.3, J9.10, J9.11, J9.12, L1.GND2, R1.2, R1.3, R3.4, R4.1, R4.2, R5.1, R5.2, S2.1, U2.2, U3.7, U3.18, U3.21, U3.25, U3.26, U4.7, U4.10, U4.11, U4.20, U4.24, U4.33, U4.35, U4.45, U4.55, U4.58, U4.61, U5.8, V3.P1, V4.P1, V5.P1, V7.P1, V8.P1, V35.P1, V37.P1, V38.P1
HIGH-I-GND: B3.G, B3.G2, B3.G3, F1.1
HIGH-V: J8.1, J9.2
LCD_RX: L1.RXI, U4.32
LCD_TX: L1.TX0, U4.31
MISO: J4.1, U4.39
MOSI: J4.4, U4.38
unnamed: D1.A1, R4.4
unnamed: D1.C2, R4.3
unnamed: D5.A1, R5.3
unnamed: D6.C2, R5.8
unnamed: D6.C1, R5.7
unnamed: D4.C1, R4.7
unnamed: D5.A2, R5.4
unnamed: D6.A2, U4.14
unnamed: D6.A1, U4.15
unnamed: R4.5, R4.6, U2.1
unnamed: R1.6, U2.5
unnamed: D4.C2, R4.8
unnamed: D2.2, S1.7
unnamed: C11.1, U4.21, U4.22
unnamed: C13.1, U4.60
PITCH: J3.V, J7.5, U4.2
PROG_SEL: S2.2, U5.4, U5.12
RESET: B1.1, B1.2, C1.1, J4.5, R3.1, U4.12
RF: D4.A2, U4.16
RF_N: B2.3, U4.9
RF_P: B2.4, U4.8
ROLL: J3.H, J7.2, U4.1
RXI: U3.5, U5.10
RXI-0: U4.47, U5.11
RXI-1: J6.RXI, U5.9
RXLED: D5.C2, U3.22
SCK: J4.3, U4.37
THROTTLE: J2.V, J5.5, U4.64
TXLED: D5.C1, U3.23
TXO: U3.1, U5.6
TXO-0: U4.46, U5.7
TXO-1: J6.TXO, U5.5
USB_D_N: J1.2, U3.16
USB_D_P: J1.3, U3.15
VBAT: D3.2, R3.6, S1.3
VBUS: C5.1, D1.A2, J1.1, R3.5, S1.6, U2.4, V1.P1, V2.P1, V23.P1, V24.P1, V26.P1, V27.P1, V28.P1
VIN: C7.1, C8.1, D2.1, D3.1, J4.2, J9.5, L1.RAW, U3.20
YAW: J2.H, J5.2, U4.63

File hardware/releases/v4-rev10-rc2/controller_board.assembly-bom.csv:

mfr,mfrpn,dist,distpn,part_list,qty,desc,value,substitute_ok,case,mounting,layer,pins,extended_pins,comments
C&K,JS202011JCQN,DIGIKEY,CKN10723CT-ND,S2 S1,2,SWITCH SLIDE DPDT 300MA 6V,SWITCH-DPDT-300MA-6V-SMD,no,,SMD,top,6,12,
Microchip Technology,ATMEGA128RFA1-ZU,DIGIKEY,ATMEGA128RFA1-ZU-ND ,U4,1,IC RF TXRX+MCU 802.15.4 64VFQFN,ATMEGA128RFA1,no,QFN,SMD,top,64,64,
Samsung Electro-Mechanics,CL10A105KP8NNNC,DIGIKEY,1276-1182-1-ND,C4 C13 C12 C11 C16,5,CAP CER 1UF 10V X5R 0603,1uF,yes,0603,SMD,top,2,10,
Abracon LLC,ABM8-16.000MHZ-B2-T,DIGIKEY,535-9134-1-ND,Y1,1,CRYSTAL 16.0000MHZ 18PF SMD,CRYSTAL-SMD-3X2,no,,SMD,top,4,4,
UNKNOWN,UNKNOWN,ALIBABA,https://www.alibaba.com/product-detail/Molex-51005-51006-2-p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,B3,1,Surface mount  battery connector,BATTERY-SMD,no,,SMD,top,4,4,
Sullins Connector Solutions,NPPC101KFXC-RC,DIGIKEY,S5641-ND,L1,1,"10 Position Header, Top or Bottom Entry Connector  Surface Mount",SPARKFUN_SERLCD_SERIAL_REDUCED-SMD,no,,SMD,top,10,10,
Toshiba Semiconductor and Storage,"CRS08(TE85L,Q,M)",DIGIKEY,CRS08QMCT-ND,D2 D3,2,DIODE SCHOTTKY 30V 1.5A SFLAT,360mV,no,,SMD,top,2,4,
Yageo,CC0603BRNPO9BNR75,DIGIKEY,311-3843-1-ND,C2,1,CAP CER 0.75PF 50V NPO 0603,0.75pF,no,0603,SMD,top,2,2,
Amphenol ICC (FCI),95278-101A06LF,DIGIKEY,609-3487-2-ND,J4,1,CONN HEADER SMD 6POS 2.54MM,AVR_SPI_PRG_6-SMD,no,,SMD,top,6,6,
Bourns Inc.,PEC12R-4217F-S0024,DIGIKEY,PEC12R-4220F-S0024-ND,E1,1,ROTARY ENCODER MECHANICAL 24PPR,ROTARY-ENCODER-W/BUTTON-BOURNS-PEC12R-4217F,NO,,TH,top,7,7,
Microchip Technology,MCP73831T-2ACI/OT,DIGIKEY,MCP73831T-2ACI/OTCT-ND,U2,1,IC CONTROLLR LI-ION 4.2V SOT23-5,MCP73831/2,no,SOT23-5,SMD,top,5,5,
AVX Corporation,06036A220KAT2A,DIGIKEY,478-11384-1-ND,C3,1,CAP CER 22PF 6.3V NP0 0603,22pF,no,0603,SMD,top,2,2,
Panasonic Electronic Components,EXB-N8V103JX,DIGIKEY,Y10103CT-ND,R3,1,RES ARRAY 4 RES 10K OHM 0804,10K,yes,0804,SMD,top,8,8,
Lite-On Inc.,LTST-C195TGKRKT,DIGIKEY,160-2252-1-ND,D6 D4 D5 D1,4,LED GREEN/RED CLEAR CHIP SMD,LED-2X-GREEN/RED-1.6X1.5MM,no,4SMD,SMD,top,4,16,
KEMET,C0603C104K8RACTU,DIGIKEY,399-1095-1-ND,C9 C8 C1,3,CAP CER 0.1UF 10V X7R 0603,0.1uF,yes,0603,SMD,top,2,6,
Amphenol ICC (FCI),10118192-0001LF,DIGIKEY,609-4613-1-ND ,J1,1,CONN RCPT USB2.0 MICRO B SMD R/A,USB-MICROA-AMPHENOL-10118192-0001LF,no,,SMD,top,11,11,
E-Switch,TL3305AF160QG,DIGIKEY,EG5350CT-ND,B4 B5 B6 B7 B1 B8 B9 B10,8,SWITCH TACTILE SPST-NO 50MA 12V,PUSHBUTTON_-4.5X4.5,yes,,SMD,top,4,32,
Samtec Inc.,TSM-102-01-L-DH,DIGIKEY,SAM15344-ND,J6,1,CONN HEADER SMD R/A 4POS 2.54MM,FTDI-4PIN-RIGHT-ANGLE-SMD,yes,,SMD,top,4,4,
FTDI,FT232RL-REEL,DIGIKEY,768-1007-1-ND ,U3,1,IC USB FS SERIAL UART 28-SSOP,FT232RLSSOP,no,,SMD,top,28,28,
Panasonic Electronic Components,EXB-N8V222JX,DIGIKEY,Y10222CT-ND,R1,1,RES ARRAY 4 RES 2.2K OHM 0804,2.2K,yes,,SMD,top,8,8,
Panasonic Electronic Components,EXB-N8V152JX,DIGIKEY,Y10152CT-ND,R4 R5,2,RES ARRAY 4 RES 1.5K OHM 0804,1.5K,yes,,SMD,top,8,16,
Samsung Electro-Mechanics,CL10A106MQ8NNNC,DIGIKEY,1276-1119-1-ND,C7 C6 C5,3,CAP CER 10UF 6.3V X5R 0603,10uF,yes,0603,SMD,top,2,6,
NXP USA Inc.,"NX3L2467PW,118",DIGIKEY,568-5300-1-ND,U5,1,IC ANALOG SWITCH DPDT 16TSSOP,DPDT-X2,no,,SMD,top,16,16,
Molex,0532610671,DIGIKEY,WM7624CT-ND,J5 J7,2,CONN HEADER SMD R/A 6POS 1.25MM,FRSKY-GIMBAL-FRYSKY-HALL-EFFECT,no,,SMD,top,8,16,
Vishay Vitramon,VJ0603A120FXQCW1BC,DIGIKEY,720-1655-1-ND,C15 C14,2,CAP CER 12PF 10V C0G/NP0 0603,12pF,no,0603,SMD,top,2,4,
Wurth Electronics Inc.,748421245,DIGIKEY,732-2230-1-ND,B2,1,BALUN 2.4GHZ-2.5GHZ 50/100 0805,BALUN0805,no,0805,SMD,top,6,6,
